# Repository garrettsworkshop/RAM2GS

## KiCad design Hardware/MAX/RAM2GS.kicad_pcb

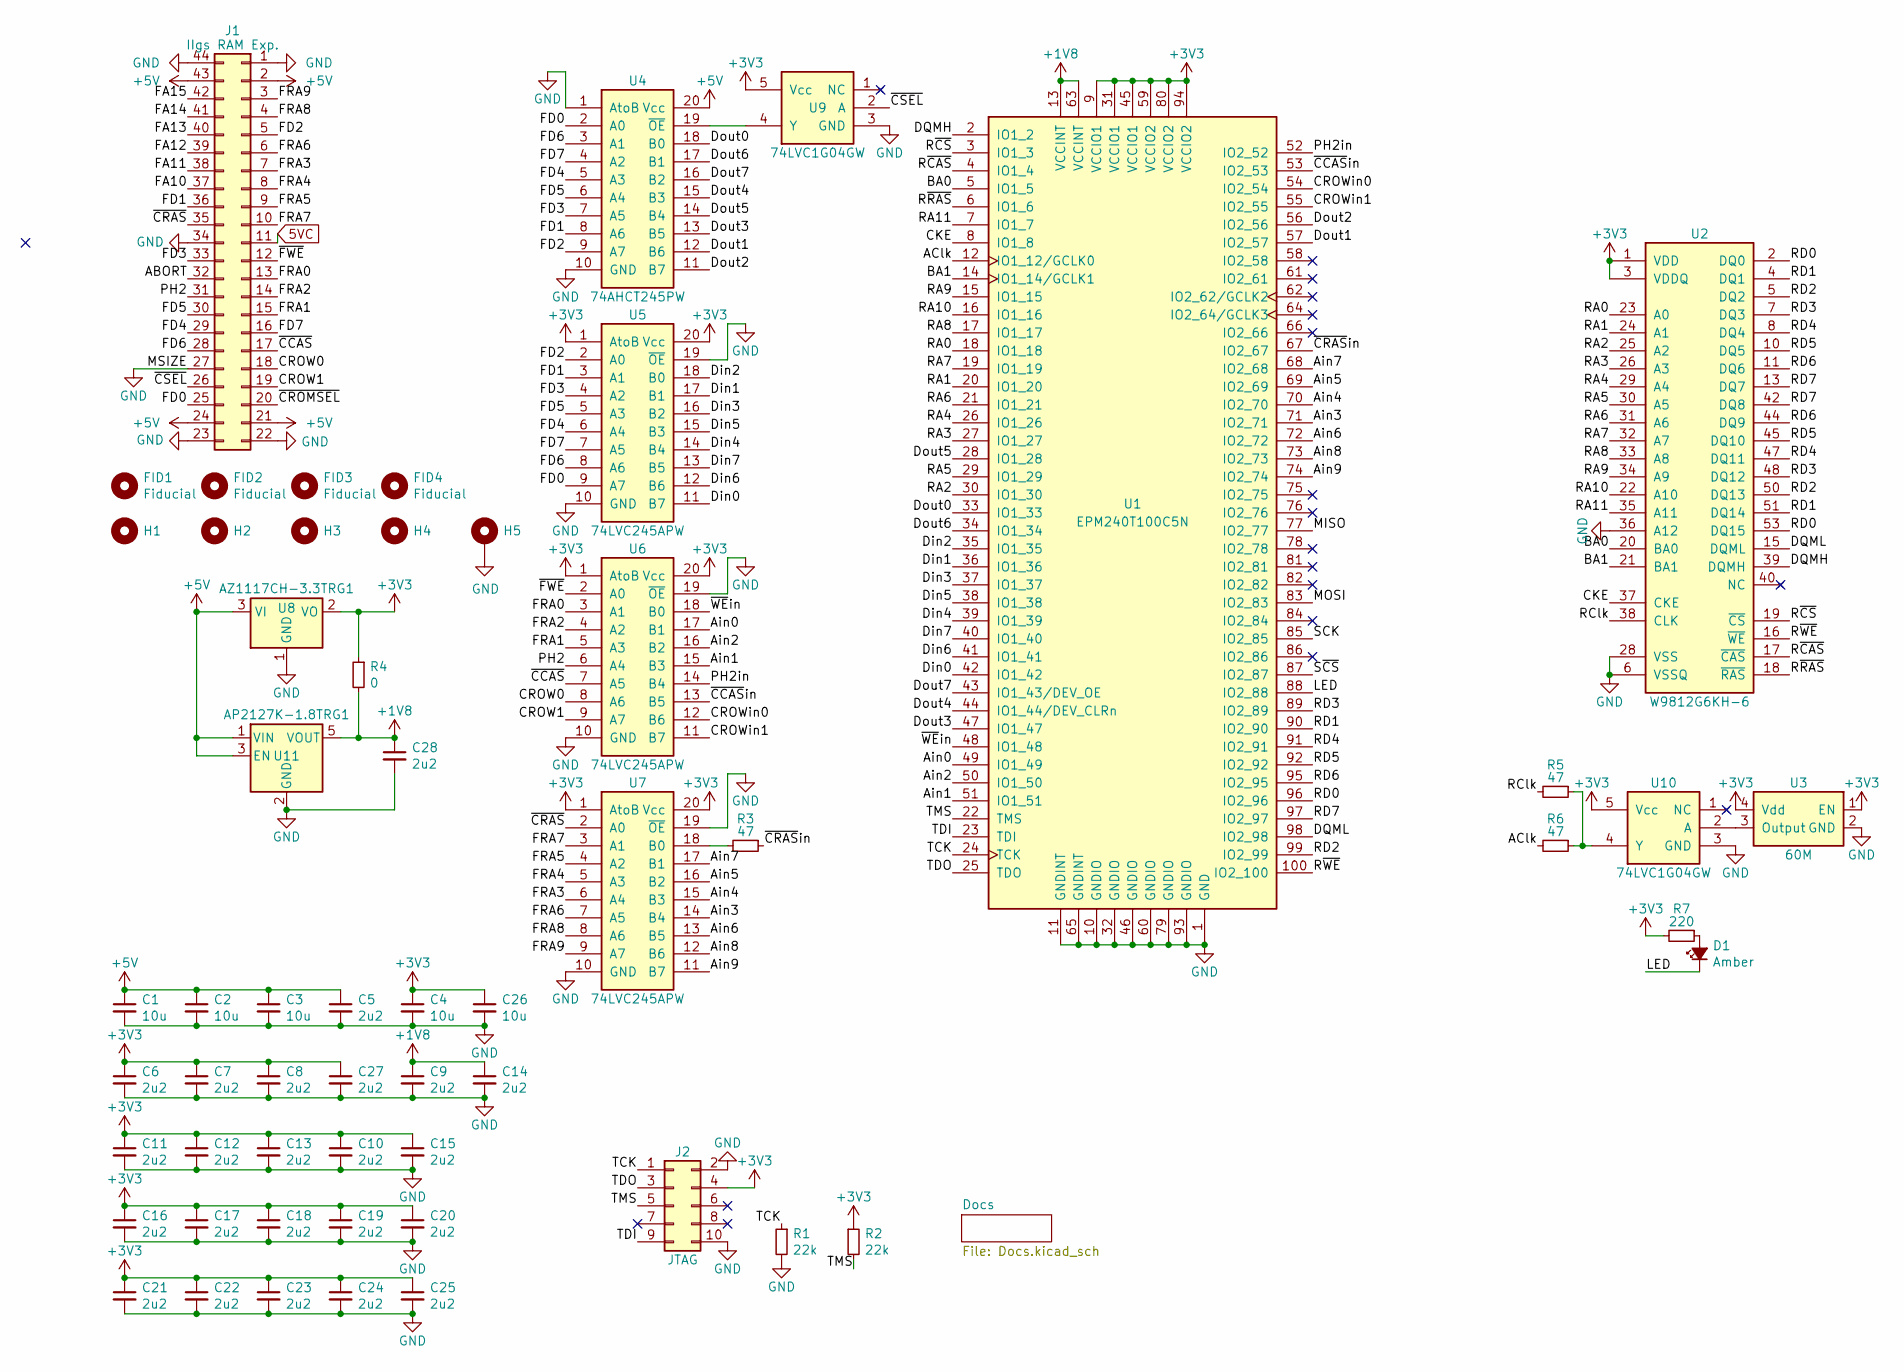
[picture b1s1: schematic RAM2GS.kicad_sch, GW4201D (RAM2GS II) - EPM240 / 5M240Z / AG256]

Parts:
C1, C2, C3, C4, C26: 10u; C_0805; LCSC Part C15850
C5, C6, C7, C8, C9, C10, C11, C12, C13, C14, C15, C16, C17, C18, C19, C20, C21, C22, C23, C24, C25, C27, C28: 2u2; C_0603; LCSC Part C23630
D1: Amber; LED_0805; LCSC Part C284932
FID1, FID2, FID3, FID4: Fiducial
H1, H2, H3, H4: PasteHole_1.152mm_NPTH
H5: PasteHole_1.1mm_PTH
J1: IIgs RAM Exp.; AppleIIgsMemoryExpansion_Edge
J2: JTAG; Tag-Connect_TC2050-IDC-FP_2x05_P1.27mm_Vertical
R1, R2: 22k; R_0805; LCSC Part C17560
R3, R5, R6: 47; R_0603; LCSC Part C23182
R4: 0; R_0805; LCSC Part C17477
R7: 220; R_0805; LCSC Part C17557
U1: EPM240T100C5N; TQFP-100_14x14mm_P0.5mm; LCSC Part C10041
U2: W9812G6KH-6; TSOP-II-54_22.2x10.16mm_P0.8mm; LCSC Part C62379
U3: 60M; Crystal_SMD_7050-4Pin_7.0x5.0mm_SiTime; LCSC Part C26255
U4: 74AHCT245PW; TSSOP-20_4.4x6.5mm_P0.65mm; LCSC Part C173388
U5, U6, U7: 74LVC245APW; TSSOP-20_4.4x6.5mm_P0.65mm; LCSC Part C6082
U8: AZ1117CH-3.3TRG1; SOT-223; LCSC Part C92102
U9, U10: 74LVC1G04GW; SOT-353; LCSC Part C10237
U11: AP2127K-1.8TRG1; SOT-23-5; LCSC Part C151375

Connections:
5VC: J1.11
+1V8: C9.1, C14.1, C28.1, R4.2, U1.13 (VCCINT), U1.63 (VCCINT), U11.5 (VOUT)
+3V3: C4.1, C6.1, C7.1, C8.1, C10.1, C11.1, C12.1, C13.1, C15.1, C16.1, C17.1, C18.1, C19.1, C20.1, C21.1, C22.1, C23.1, C24.1, C25.1, C26.1, C27.1, J2.4, R2.1, R4.1, R7.2, U1.9 (VCCIO1), U1.31 (VCCIO1), U1.45 (VCCIO1), U1.59 (VCCIO2), U1.80 (VCCIO2), U1.94 (VCCIO2), U2.1 (VDD), U2.3 (VDDQ), U2.9 (VDDQ), U2.14 (VDD), U2.27 (VDD), U2.43 (VDDQ), U2.49 (VDDQ), U3.1 (EN), U3.4 (Vdd), U5.1 (AtoB), U5.20 (Vcc), U6.1 (AtoB), U6.20 (Vcc), U7.1 (AtoB), U7.20 (Vcc), U8.2 (VO), U9.5 (Vcc), U10.5 (Vcc)
+5V: C1.1, C2.1, C3.1, C5.1, J1.2, J1.21, J1.24, J1.43, U4.20 (Vcc), U8.3 (VI), U11.1 (VIN), U11.3 (EN)
/ABORT: J1.32
/AClk: R6.2, U1.12 (IO1_12/GCLK0)
/Ain0: U1.49 (IO1_49), U6.17 (B1)
/Ain1: U1.51 (IO1_51), U6.15 (B3)
/Ain2: U1.50 (IO1_50), U6.16 (B2)
/Ain3: U1.71 (IO2_71), U7.14 (B4)
/Ain4: U1.70 (IO2_70), U7.15 (B3)
/Ain5: U1.69 (IO2_69), U7.16 (B2)
/Ain6: U1.72 (IO2_72), U7.13 (B5)
/Ain7: U1.68 (IO2_68), U7.17 (B1)
/Ain8: U1.73 (IO2_73), U7.12 (B6)
/Ain9: U1.74 (IO2_74), U7.11 (B7)
/BA0: U1.5 (IO1_5), U2.20 (BA0)
/BA1: U1.14 (IO1_14/GCLK1), U2.21 (BA1)
/CKE: U1.8 (IO1_8), U2.37 (CKE)
/CROW0: J1.18, U6.8 (A6)
/CROW1: J1.19, U6.9 (A7)
/CROWin0: U1.54 (IO2_54), U6.12 (B6)
/CROWin1: U1.55 (IO2_55), U6.11 (B7)
/DQMH: U1.2 (IO1_2), U2.39 (DQMH)
/DQML: U1.98 (IO2_98), U2.15 (DQML)
/Din0: U1.42 (IO1_42), U5.11 (B7)
/Din1: U1.36 (IO1_36), U5.17 (B1)
/Din2: U1.35 (IO1_35), U5.18 (B0)
/Din3: U1.37 (IO1_37), U5.16 (B2)
/Din4: U1.39 (IO1_39), U5.14 (B4)
/Din5: U1.38 (IO1_38), U5.15 (B3)
/Din6: U1.41 (IO1_41), U5.12 (B6)
/Din7: U1.40 (IO1_40), U5.13 (B5)
/Dout0: U1.33 (IO1_33), U4.18 (B0)
/Dout1: U1.57 (IO2_57), U4.12 (B6)
/Dout2: U1.56 (IO2_56), U4.11 (B7)
/Dout3: U1.47 (IO1_47), U4.13 (B5)
/Dout4: U1.44 (IO1_44/DEV_CLRn), U4.15 (B3)
/Dout5: U1.28 (IO1_28), U4.14 (B4)
/Dout6: U1.34 (IO1_34), U4.17 (B1)
/Dout7: U1.43 (IO1_43/DEV_OE), U4.16 (B2)
/FA10: J1.37
/FA11: J1.38
/FA12: J1.39
/FA13: J1.40
/FA14: J1.41
/FA15: J1.42
/FD0: J1.25, U4.2 (A0), U5.9 (A7)
/FD1: J1.36, U4.8 (A6), U5.3 (A1)
/FD2: J1.5, U4.9 (A7), U5.2 (A0)
/FD3: J1.33, U4.7 (A5), U5.4 (A2)
/FD4: J1.29, U4.5 (A3), U5.6 (A4)
/FD5: J1.30, U4.6 (A4), U5.5 (A3)
/FD6: J1.28, U4.3 (A1), U5.8 (A6)
/FD7: J1.16, U4.4 (A2), U5.7 (A5)
/FRA0: J1.13, U6.3 (A1)
/FRA1: J1.15, U6.5 (A3)
/FRA2: J1.14, U6.4 (A2)
/FRA3: J1.7, U7.6 (A4)
/FRA4: J1.8, U7.5 (A3)
/FRA5: J1.9, U7.4 (A2)
/FRA6: J1.6, U7.7 (A5)
/FRA7: J1.10, U7.3 (A1)
/FRA8: J1.4, U7.8 (A6)
/FRA9: J1.3, U7.9 (A7)
/LED: D1.1 (K), U1.88 (IO2_88)
/MISO: U1.77 (IO2_77)
/MOSI: U1.83 (IO2_83)
/PH2: J1.31, U6.6 (A4)
/PH2in: U1.52 (IO2_52), U6.14 (B4)
/RA0: U1.18 (IO1_18), U2.23 (A0)
/RA1: U1.20 (IO1_20), U2.24 (A1)
/RA2: U1.30 (IO1_30), U2.25 (A2)
/RA3: U1.27 (IO1_27), U2.26 (A3)
/RA4: U1.26 (IO1_26), U2.29 (A4)
/RA5: U1.29 (IO1_29), U2.30 (A5)
/RA6: U1.21 (IO1_21), U2.31 (A6)
/RA7: U1.19 (IO1_19), U2.32 (A7)
/RA8: U1.17 (IO1_17), U2.33 (A8)
/RA9: U1.15 (IO1_15), U2.34 (A9)
/RA10: U1.16 (IO1_16), U2.22 (A10)
/RA11: U1.7 (IO1_7), U2.35 (A11)
/RClk: R5.2, U2.38 (CLK)
/RD0: U1.96 (IO2_96), U2.2 (DQ0), U2.53 (DQ15)
/RD1: U1.90 (IO2_90), U2.4 (DQ1), U2.51 (DQ14)
/RD2: U1.99 (IO2_99), U2.5 (DQ2), U2.50 (DQ13)
/RD3: U1.89 (IO2_89), U2.7 (DQ3), U2.48 (DQ12)
/RD4: U1.91 (IO2_91), U2.8 (DQ4), U2.47 (DQ11)
/RD5: U1.92 (IO2_92), U2.10 (DQ5), U2.45 (DQ10)
/RD6: U1.95 (IO2_95), U2.11 (DQ6), U2.44 (DQ9)
/RD7: U1.97 (IO2_97), U2.13 (DQ7), U2.42 (DQ8)
/R~CAS: U1.4 (IO1_4), U2.17 (~CAS)
/R~CS: U1.3 (IO1_3), U2.19 (~CS)
/R~RAS: U1.6 (IO1_6), U2.18 (~RAS)
/R~WE: U1.100 (IO2_100), U2.16 (~WE)
/SCK: U1.85 (IO2_85)
/S~CS: U1.87 (IO2_87)
/TCK: J2.1, R1.1, U1.24 (TCK)
/TDI: J2.9, U1.23 (TDI)
/TDO: J2.3, U1.25 (TDO)
/TMS: J2.5, R2.2, U1.22 (TMS)
/~CCAS: J1.17, U6.7 (A5)
/~CCASin: U1.53 (IO2_53), U6.13 (B5)
/~CRAS: J1.35, U7.2 (A0)
/~CRASin: R3.1, U1.67 (IO2_67)
/~CROMSEL: J1.20
/~CSEL: J1.26, U9.2 (A)
/~FWE: J1.12, U6.2 (A0)
/~WEin: U1.48 (IO1_48), U6.18 (B0)
GND: C1.2, C2.2, C3.2, C4.2, C5.2, C6.2, C7.2, C8.2, C9.2, C10.2, C11.2, C12.2, C13.2, C14.2, C15.2, C16.2, C17.2, C18.2, C19.2, C20.2, C21.2, C22.2, C23.2, C24.2, C25.2, C26.2, C27.2, C28.2, H5.1, J1.1, J1.22, J1.23, J1.27, J1.34, J1.44, J2.2, J2.10, R1.2, U1.1 (GND), U1.10 (GNDIO), U1.11 (GNDINT), U1.32 (GNDIO), U1.46 (GNDIO), U1.60 (GNDIO), U1.65 (GNDINT), U1.79 (GNDIO), U1.93 (GNDIO), U2.6 (VSSQ), U2.12 (VSSQ), U2.28 (VSS), U2.36 (A12), U2.41 (VSS), U2.46 (VSSQ), U2.52 (VSSQ), U2.54 (VSS), U3.2 (GND), U4.1 (AtoB), U4.10 (GND), U5.10 (GND), U5.19 (~OE), U6.10 (GND), U6.19 (~OE), U7.10 (GND), U7.19 (~OE), U8.1 (GND), U9.3 (GND), U10.3 (GND), U11.2 (GND)
unnamed: D1.2 (A), R7.1
unnamed: U4.19 (~OE), U9.4 (Y)
unnamed: R3.2, U7.18 (B0)
unnamed: U3.3 (Output), U10.2 (A)
unnamed: R5.1, R6.1, U10.4 (Y)

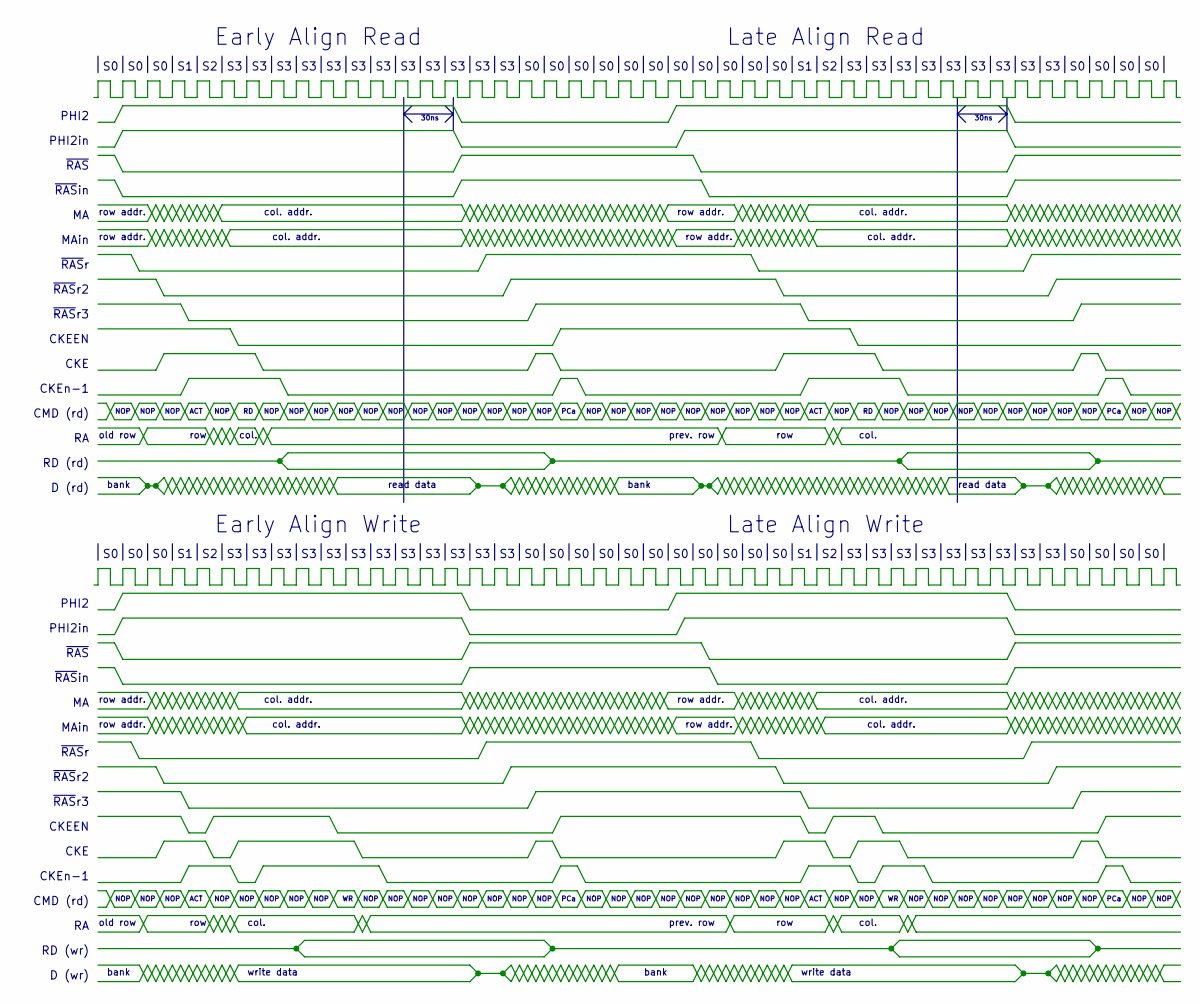
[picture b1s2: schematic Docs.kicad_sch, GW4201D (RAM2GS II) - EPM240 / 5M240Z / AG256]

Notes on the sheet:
NOP
~{RAS}r3
col.
30ns
~{RAS}r
~{RAS}in
Early Align Read
D (rd)
col. addr.
row addr.
prev. row
CKEn-1
PHI2
MAin
bank
~{RAS}r2
CMD (rd)
read data
Late Align Write
row
PHI2in
RD (wr)
PCa
write data
CKEEN
RD (rd)
Late Align Read
D (wr)
ACT
~{RAS}
CKE
old row
Early Align Write

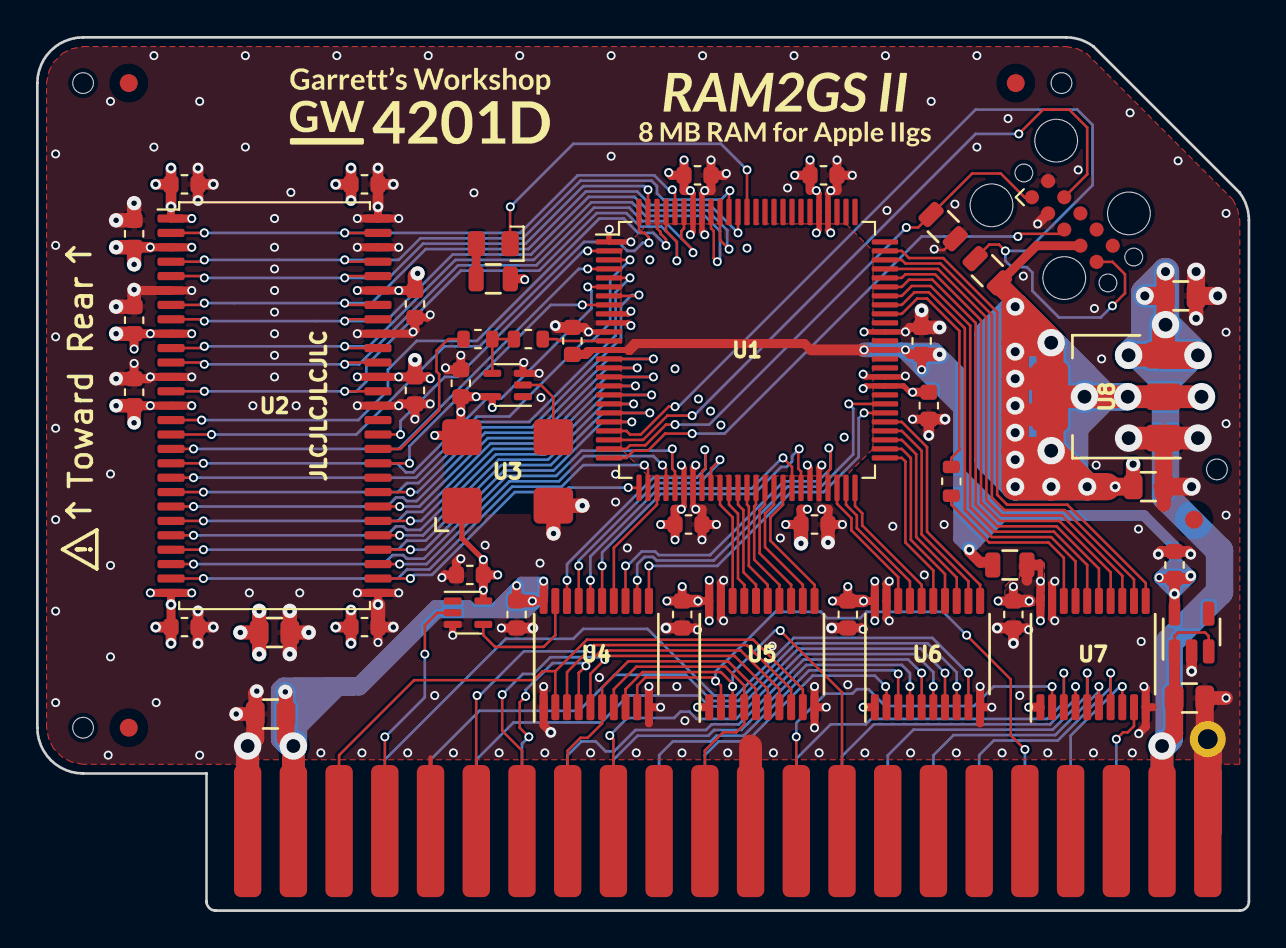
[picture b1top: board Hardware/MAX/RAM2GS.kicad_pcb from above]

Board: 4 copper layers, 67.3 x 48.5 mm, 58 parts (0 on the bottom side), 102 nets.

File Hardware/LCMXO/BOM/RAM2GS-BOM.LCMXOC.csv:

Reference, Quantity, Value, Footprint, Datasheet, Notes, LCSC Part, Mfg. Part Numbers
C30 ,1,15p,stdpads:C_0603,,"10V or higher. Any manufacturer's part is acceptable but Samsung, Murata, Yageo preferred.",C1644,Samsung CL10C150JB8NNNC
C1 C2 C3 C4 C26 ,5,10u,stdpads:C_0805,,"10V or higher. Any manufacturer's part is acceptable but Samsung, Murata, Yageo preferred.",C15850,Samsung CL21A106KAYNNNE
C5 C6 C7 C8 C9 C10 C11 C12 C13 C14 C15 C16 C17 C18 C19 C20 C21 C22 C23 C24 C25 C27 C28 C29 ,24,2u2,stdpads:C_0603,,"10V or higher. Any manufacturer's part is acceptable but Samsung, Murata, Yageo preferred.",C23630,Samsung CL10A225KO8NNNC
D1 ,1,Amber,stdpads:LED_0805,,Any manufacturer's part is acceptable.,,
FID1 FID2 FID3 FID4 ,4,Fiducial,stdpads:Fiducial,,DNP - SMT vision system fiducial,,
H1 H2 H4 H5 ,4, ,stdpads:PasteHole_1.152mm_NPTH,,DNP - mounting hole for solder paste printing,,
H3 ,1, ,stdpads:PasteHole_1.1mm_PTH,,DNP - mounting hole,,
J1 ,1,IIgs RAM Exp.,stdpads:AppleIIgsMemoryExpansion_Edge,,DNP - edge connector,,
J2 ,1,JTAG,Connector:Tag-Connect_TC2050-IDC-FP_2x05_P1.27mm_Vertical,,DNP - test pad connector,,
R1 R2 ,2,22k,stdpads:R_0805,,Any manufacturer's part is acceptable.,C17560,Uniroyal 0805W8F2202T5E
R4 ,1,0,stdpads:R_0805,,Any manufacturer's part is acceptable.,C17477,Uniroyal 0805W8F0000T5E
R3 R5 R6 R7 ,4,47,stdpads:R_0603,,Any manufacturer's part is acceptable.,C23182,Uniroyal 0603WAF470JT5E
R8 ,1,220,stdpads:R_0805,,Any manufacturer's part is acceptable.,C17557,Uniroyal 0805W8F2200T5E
U1 ,1,LCMXO256C-TN100,stdpads:TQFP-100_14x14mm_P0.5mm,,,C1550734,"Lattice LCMXO256C-3TN100C, Lattice LCMXO256C-4TN100C, Lattice LCMXO256C-5TN100C, Lattice LCMXO256C-3TN100I, Lattice LCMXO256C-4TN100I, Lattice LCMXO640C-3TN100C, Lattice LCMXO640C-4TN100C, Lattice LCMXO640C-5TN100C, Lattice LCMXO640C-3TN100I, Lattice LCMXO640C-4TN100I"
U9 U10 ,2,74LVC1G04GW,stdpads:SOT-353,,Most 74LVC1G04 or 74AHC1G04 in SOT-353 package is acceptable.,C10237,"NXP 74LVC1G04GW, TI SN74LVC1G04DCK, NXP 74AHC1G04GW, TI SN74AHC1G04DCK"
U11 ,1,DNP,stdpads:SOT-23-5,,,,
U12 ,1,25F010,stdpads:SOIC-8_3.9mm,,Most SPI flash in SOIC-8 (3.9mm / 150 mil width) package is acceptable.,C2687406,"Zetta ZD25WD20BTIGT, Adesto AT25SF081-SSHD, Winbond W25X20CLSNIG"
U2 ,1,W9812G6KH-6,stdpads:TSOP-II-54_22.2x10.16mm_P0.8mm,,Most 166 MHz 128/256 Mbit x16 SDRAM is acceptable.,C62379,"Winbond W9812G6KH-6, Winbond W9812G6KH-6I, Winbond W9825G6KH-6, Winbond W9825G6KH-6I, ISSI IS42S16160J-6TL, ISSI IS42S16160J-6TLI, Micron MT48LC16M16A2P-6A :G, Micron MT48LC16M16A2P-6A IT:G"
U3 ,1,60M,stdpads:Crystal_SMD_7050-4Pin_7.0x5.0mm_SiTime,,Most 60-62.5 MHz 3.3V crystal oscillator or silicon oscillator is acceptable. Do not use crystal resonator or ceramic resonator.,C26255,"SiTime SIT1602AI-82-33E-60.000000Y, Shenzhen SCTF S7D60.000000B20F30T, Taiten OCETGLJTNF-60MHZ"
U4 ,1,74AHCT245PW,stdpads:TSSOP-20_4.4x6.5mm_P0.65mm,,Most 74AHCT245 in TSSOP-20 package is acceptable.,C173388,"NXP 74AHCT245PW, NXP 74AHCT245APW, TI SN74AHCT245PW"
U5 U6 U7 ,3,74LVC245APW,stdpads:TSSOP-20_4.4x6.5mm_P0.65mm,,Most 74LVC245 or 74AHC245 in TSSOP-20 package is acceptable.,C6082,"NXP 74LVC245APW, TI SN74LVC245APW, NXP 74AHC245PW, NXP 74AHC245APW, TI SN74AHC245PW"
U8 ,1,AZ1117CH-3.3TRG1,stdpads:SOT-223,,Most 1117-type 3.3V regulator in SOT-223 package is acceptable.,C92102,"Diodes AZ1117CH-3.3TRG1, Diodes AZ1117EH-3.3TRG1"

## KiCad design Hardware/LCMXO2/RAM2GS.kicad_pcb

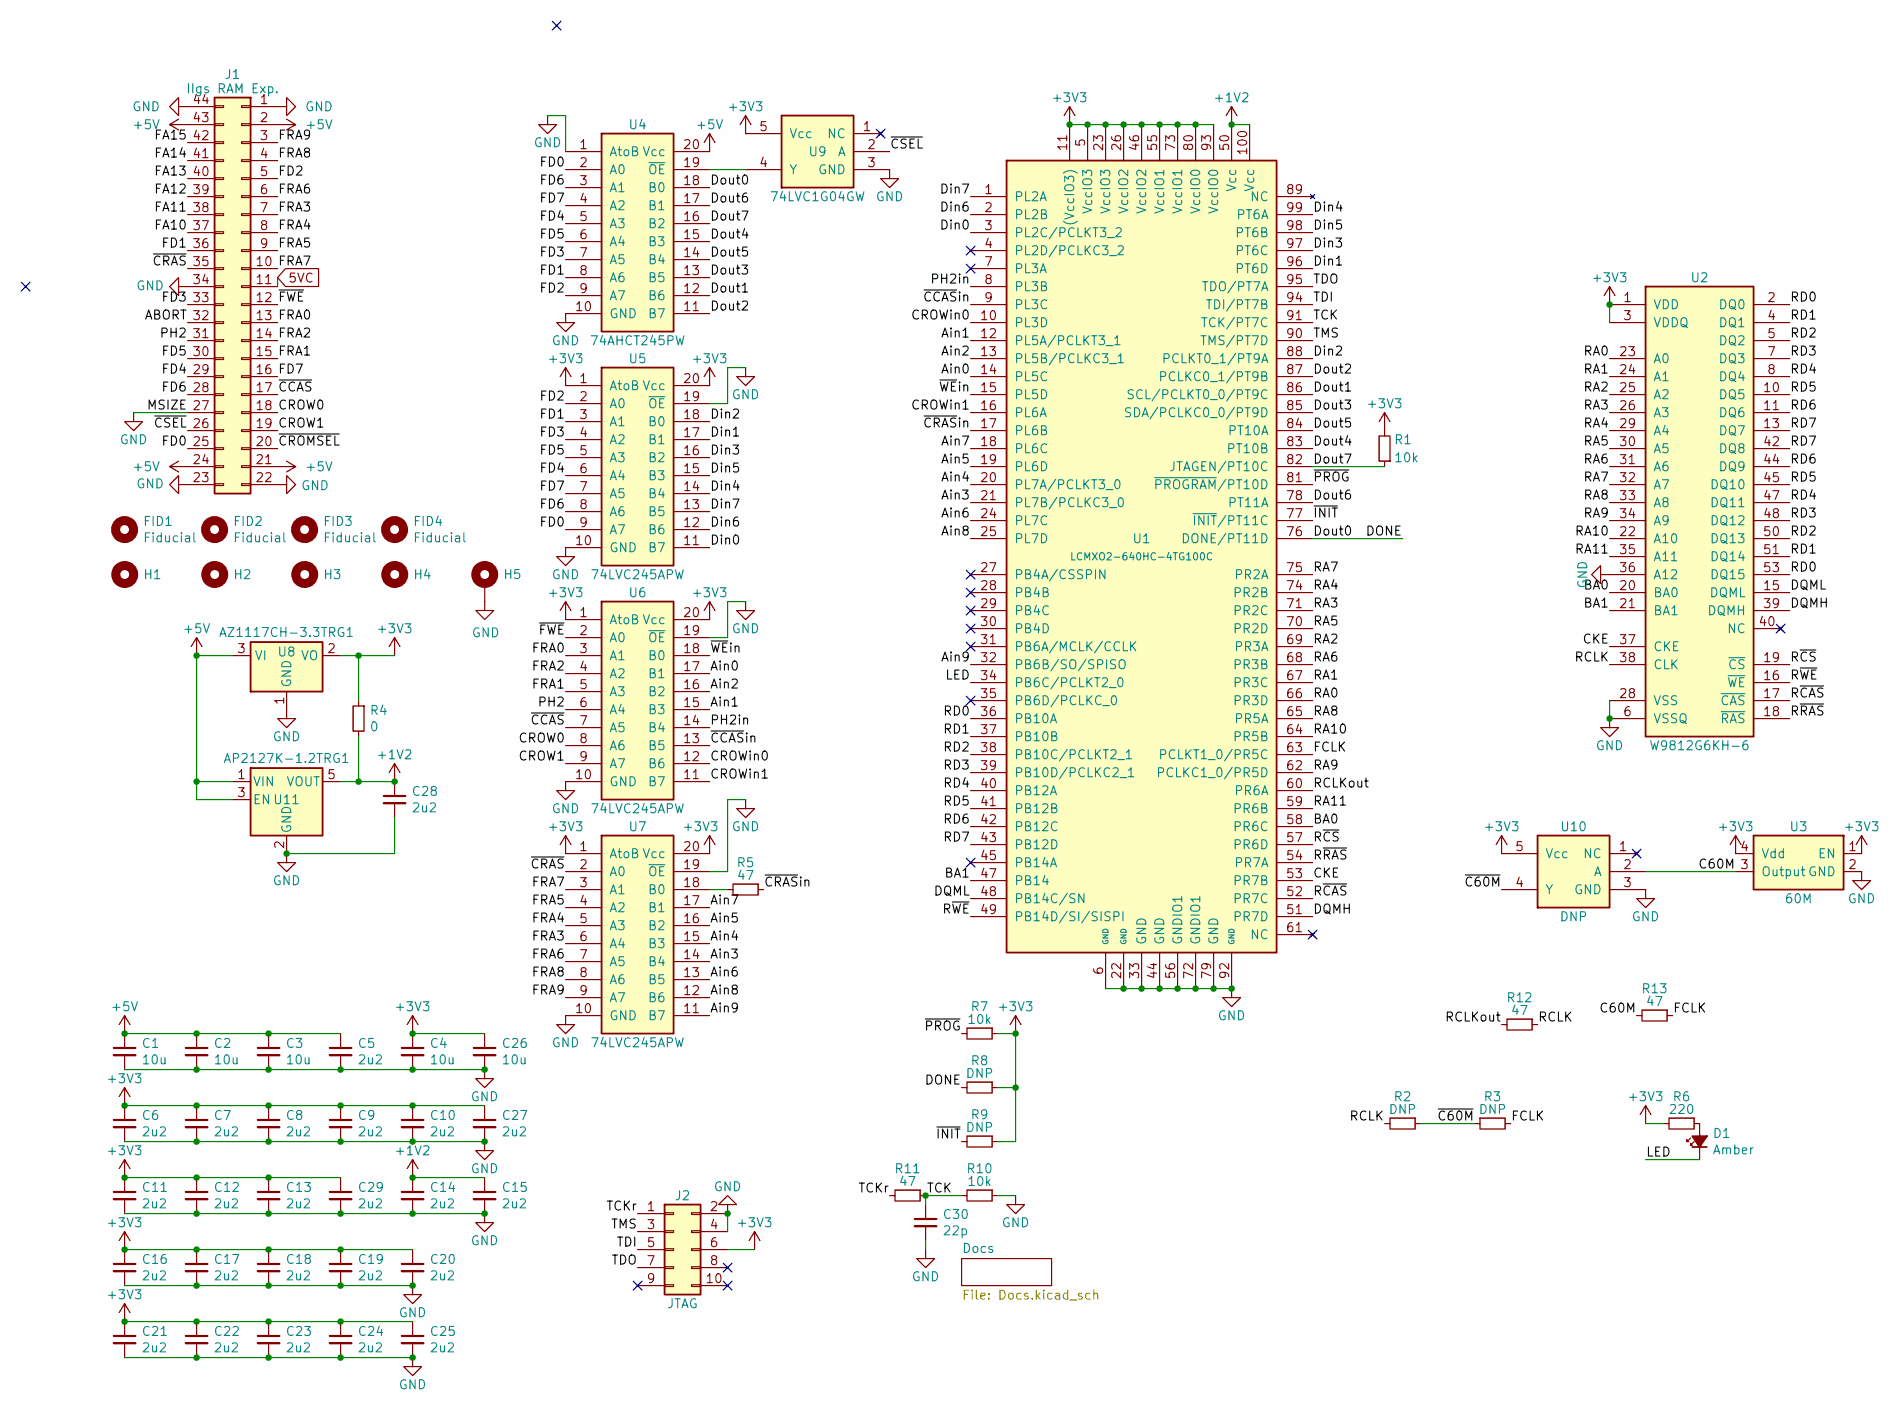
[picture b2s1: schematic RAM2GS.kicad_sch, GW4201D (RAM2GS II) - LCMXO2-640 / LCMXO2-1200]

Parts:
C1, C2, C3, C4, C26: 10u; C_0805; LCSC Part C15850
C5, C6, C7, C8, C9, C10, C11, C12, C13, C14, C15, C16, C17, C18, C19, C20, C21, C22, C23, C24, C25, C27, C28, C29: 2u2; C_0603; LCSC Part C23630
C30: 22p; C_0603; LCSC Part C1653
D1: Amber; LED_0805; LCSC Part C284932
FID1, FID2, FID3, FID4: Fiducial
H1, H2, H3, H4: PasteHole_1.152mm_NPTH
H5: PasteHole_1.1mm_PTH
J1: IIgs RAM Exp.; AppleIIgsMemoryExpansion_Edge
J2: JTAG; Tag-Connect_TC2050-IDC-FP_2x05_P1.27mm_Vertical
R1, R7, R10: 10k; R_0603; LCSC Part C25804
R2, R3, R8, R9: DNP; R_0603
R4: 0; R_0805; LCSC Part C17477
R5, R11, R12, R13: 47; R_0603; LCSC Part C23182
R6: 220; R_0805; LCSC Part C17557
U1: LCMXO2-640HC-4TG100C; TQFP-100_14x14mm_P0.5mm; LCSC Part C1519051
U2: W9812G6KH-6; TSOP-II-54_22.2x10.16mm_P0.8mm; LCSC Part C62379
U3: 60M; Crystal_SMD_7050-4Pin_7.0x5.0mm_SiTime; LCSC Part C26255
U4: 74AHCT245PW; TSSOP-20_4.4x6.5mm_P0.65mm; LCSC Part C173388
U5, U6, U7: 74LVC245APW; TSSOP-20_4.4x6.5mm_P0.65mm; LCSC Part C6082
U8: AZ1117CH-3.3TRG1; SOT-223; LCSC Part C92102
U9: 74LVC1G04GW; SOT-353; LCSC Part C10237
U10: DNP; SOT-353
U11: AP2127K-1.2TRG1; SOT-23-5; LCSC Part C151376

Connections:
5VC: J1.11
+1V2: C14.1, C15.1, C28.1, R4.2, U1.50 (Vcc), U1.100 (Vcc), U11.5 (VOUT)
+3V3: C4.1, C6.1, C7.1, C8.1, C9.1, C10.1, C11.1, C12.1, C13.1, C16.1, C17.1, C18.1, C19.1, C20.1, C21.1, C22.1, C23.1, C24.1, C25.1, C26.1, C27.1, C29.1, J2.6, R1.2, R4.1, R6.2, R7.1, R8.1, R9.1, U1.5 (VccIO3), U1.11 ((VccIO3)), U1.23 (VccIO3), U1.26 (VccIO2), U1.46 (VccIO2), U1.55 (VccIO1), U1.73 (VccIO1), U1.80 (VccIO0), U1.93 (VccIO0), U2.1 (VDD), U2.3 (VDDQ), U2.9 (VDDQ), U2.14 (VDD), U2.27 (VDD), U2.43 (VDDQ), U2.49 (VDDQ), U3.1 (EN), U3.4 (Vdd), U5.1 (AtoB), U5.20 (Vcc), U6.1 (AtoB), U6.20 (Vcc), U7.1 (AtoB), U7.20 (Vcc), U8.2 (VO), U9.5 (Vcc), U10.5 (Vcc)
+5V: C1.1, C2.1, C3.1, C5.1, J1.2, J1.21, J1.24, J1.43, U4.20 (Vcc), U8.3 (VI), U11.1 (VIN), U11.3 (EN)
/ABORT: J1.32
/Ain0: U1.14 (PL5C), U6.17 (B1)
/Ain1: U1.12 (PL5A/PCLKT3_1), U6.15 (B3)
/Ain2: U1.13 (PL5B/PCLKC3_1), U6.16 (B2)
/Ain3: U1.21 (PL7B/PCLKC3_0), U7.14 (B4)
/Ain4: U1.20 (PL7A/PCLKT3_0), U7.15 (B3)
/Ain5: U1.19 (PL6D), U7.16 (B2)
/Ain6: U1.24 (PL7C), U7.13 (B5)
/Ain7: U1.18 (PL6C), U7.17 (B1)
/Ain8: U1.25 (PL7D), U7.12 (B6)
/Ain9: U1.32 (PB6B/SO/SPISO), U7.11 (B7)
/BA0: U1.58 (PR6C), U2.20 (BA0)
/BA1: U1.47 (PB14), U2.21 (BA1)
/C60M: R13.2, U3.3 (Output), U10.2 (A)
/CKE: U1.53 (PR7B), U2.37 (CKE)
/CROW0: J1.18, U6.8 (A6)
/CROW1: J1.19, U6.9 (A7)
/CROWin0: U1.10 (PL3D), U6.12 (B6)
/CROWin1: U1.16 (PL6A), U6.11 (B7)
/DONE: R8.2, U1.76 (DONE/PT11D), U4.18 (B0)
/DQMH: U1.51 (PR7D), U2.39 (DQMH)
/DQML: U1.48 (PB14C/SN), U2.15 (DQML)
/Din0: U1.3 (PL2C/PCLKT3_2), U5.11 (B7)
/Din1: U1.96 (PT6D), U5.17 (B1)
/Din2: U1.88 (PCLKT0_1/PT9A), U5.18 (B0)
/Din3: U1.97 (PT6C), U5.16 (B2)
/Din4: U1.99 (PT6A), U5.14 (B4)
/Din5: U1.98 (PT6B), U5.15 (B3)
/Din6: U1.2 (PL2B), U5.12 (B6)
/Din7: U1.1 (PL2A), U5.13 (B5)
/Dout1: U1.86 (SCL/PCLKT0_0/PT9C), U4.12 (B6)
/Dout2: U1.87 (PCLKC0_1/PT9B), U4.11 (B7)
/Dout3: U1.85 (SDA/PCLKC0_0/PT9D), U4.13 (B5)
/Dout4: U1.83 (PT10B), U4.15 (B3)
/Dout5: U1.84 (PT10A), U4.14 (B4)
/Dout6: U1.78 (PT11A), U4.17 (B1)
/Dout7: R1.1, U1.82 (JTAGEN/PT10C), U4.16 (B2)
/FA10: J1.37
/FA11: J1.38
/FA12: J1.39
/FA13: J1.40
/FA14: J1.41
/FA15: J1.42
/FCLK: R3.2, R13.1, U1.63 (PCLKT1_0/PR5C)
/FD0: J1.25, U4.2 (A0), U5.9 (A7)
/FD1: J1.36, U4.8 (A6), U5.3 (A1)
/FD2: J1.5, U4.9 (A7), U5.2 (A0)
/FD3: J1.33, U4.7 (A5), U5.4 (A2)
/FD4: J1.29, U4.5 (A3), U5.6 (A4)
/FD5: J1.30, U4.6 (A4), U5.5 (A3)
/FD6: J1.28, U4.3 (A1), U5.8 (A6)
/FD7: J1.16, U4.4 (A2), U5.7 (A5)
/FRA0: J1.13, U6.3 (A1)
/FRA1: J1.15, U6.5 (A3)
/FRA2: J1.14, U6.4 (A2)
/FRA3: J1.7, U7.6 (A4)
/FRA4: J1.8, U7.5 (A3)
/FRA5: J1.9, U7.4 (A2)
/FRA6: J1.6, U7.7 (A5)
/FRA7: J1.10, U7.3 (A1)
/FRA8: J1.4, U7.8 (A6)
/FRA9: J1.3, U7.9 (A7)
/LED: D1.1 (K), U1.34 (PB6C/PCLKT2_0)
/PH2: J1.31, U6.6 (A4)
/PH2in: U1.8 (PL3B), U6.14 (B4)
/RA0: U1.66 (PR3D), U2.23 (A0)
/RA1: U1.67 (PR3C), U2.24 (A1)
/RA2: U1.69 (PR3A), U2.25 (A2)
/RA3: U1.71 (PR2C), U2.26 (A3)
/RA4: U1.74 (PR2B), U2.29 (A4)
/RA5: U1.70 (PR2D), U2.30 (A5)
/RA6: U1.68 (PR3B), U2.31 (A6)
/RA7: U1.75 (PR2A), U2.32 (A7)
/RA8: U1.65 (PR5A), U2.33 (A8)
/RA9: U1.62 (PCLKC1_0/PR5D), U2.34 (A9)
/RA10: U1.64 (PR5B), U2.22 (A10)
/RA11: U1.59 (PR6B), U2.35 (A11)
/RCLK: R2.2, R12.1, U2.38 (CLK)
/RCLKout: R12.2, U1.60 (PR6A)
/RD0: U1.36 (PB10A), U2.2 (DQ0), U2.53 (DQ15)
/RD1: U1.37 (PB10B), U2.4 (DQ1), U2.51 (DQ14)
/RD2: U1.38 (PB10C/PCLKT2_1), U2.5 (DQ2), U2.50 (DQ13)
/RD3: U1.39 (PB10D/PCLKC2_1), U2.7 (DQ3), U2.48 (DQ12)
/RD4: U1.40 (PB12A), U2.8 (DQ4), U2.47 (DQ11)
/RD5: U1.41 (PB12B), U2.10 (DQ5), U2.45 (DQ10)
/RD6: U1.42 (PB12C), U2.11 (DQ6), U2.44 (DQ9)
/RD7: U1.43 (PB12D), U2.13 (DQ7), U2.42 (DQ8)
/R~CAS: U1.52 (PR7C), U2.17 (~CAS)
/R~CS: U1.57 (PR6D), U2.19 (~CS)
/R~RAS: U1.54 (PR7A), U2.18 (~RAS)
/R~WE: U1.49 (PB14D/SI/SISPI), U2.16 (~WE)
/TCK: C30.1, R10.2, R11.1, U1.91 (TCK/PT7C)
/TCKr: J2.1, R11.2
/TDI: J2.5, U1.94 (TDI/PT7B)
/TDO: J2.7, U1.95 (TDO/PT7A)
/TMS: J2.3, U1.90 (TMS/PT7D)
/~C60M: R2.1, R3.1, U10.4 (Y)
/~CCAS: J1.17, U6.7 (A5)
/~CCASin: U1.9 (PL3C), U6.13 (B5)
/~CRAS: J1.35, U7.2 (A0)
/~CRASin: R5.1, U1.17 (PL6B)
/~CROMSEL: J1.20
/~CSEL: J1.26, U9.2 (A)
/~FWE: J1.12, U6.2 (A0)
/~INIT: R9.2, U1.77 (~INIT/PT11C)
/~PROG: R7.2, U1.81 (~PROGRAM/PT10D)
/~WEin: U1.15 (PL5D), U6.18 (B0)
GND: C1.2, C2.2, C3.2, C4.2, C5.2, C6.2, C7.2, C8.2, C9.2, C10.2, C11.2, C12.2, C13.2, C14.2, C15.2, C16.2, C17.2, C18.2, C19.2, C20.2, C21.2, C22.2, C23.2, C24.2, C25.2, C26.2, C27.2, C28.2, C29.2, C30.2, H5.1, J1.1, J1.22, J1.23, J1.27, J1.34, J1.44, J2.2, J2.4, R10.1, U1.6 (GND), U1.22 (GND), U1.33 (GND), U1.44 (GND), U1.56 (GNDIO1), U1.72 (GNDIO1), U1.79 (GND), U1.92 (GND), U2.6 (VSSQ), U2.12 (VSSQ), U2.28 (VSS), U2.36 (A12), U2.41 (VSS), U2.46 (VSSQ), U2.52 (VSSQ), U2.54 (VSS), U3.2 (GND), U4.1 (AtoB), U4.10 (GND), U5.10 (GND), U5.19 (~OE), U6.10 (GND), U6.19 (~OE), U7.10 (GND), U7.19 (~OE), U8.1 (GND), U9.3 (GND), U10.3 (GND), U11.2 (GND)
unnamed: D1.2 (A), R6.1
unnamed: U4.19 (~OE), U9.4 (Y)
unnamed: R5.2, U7.18 (B0)

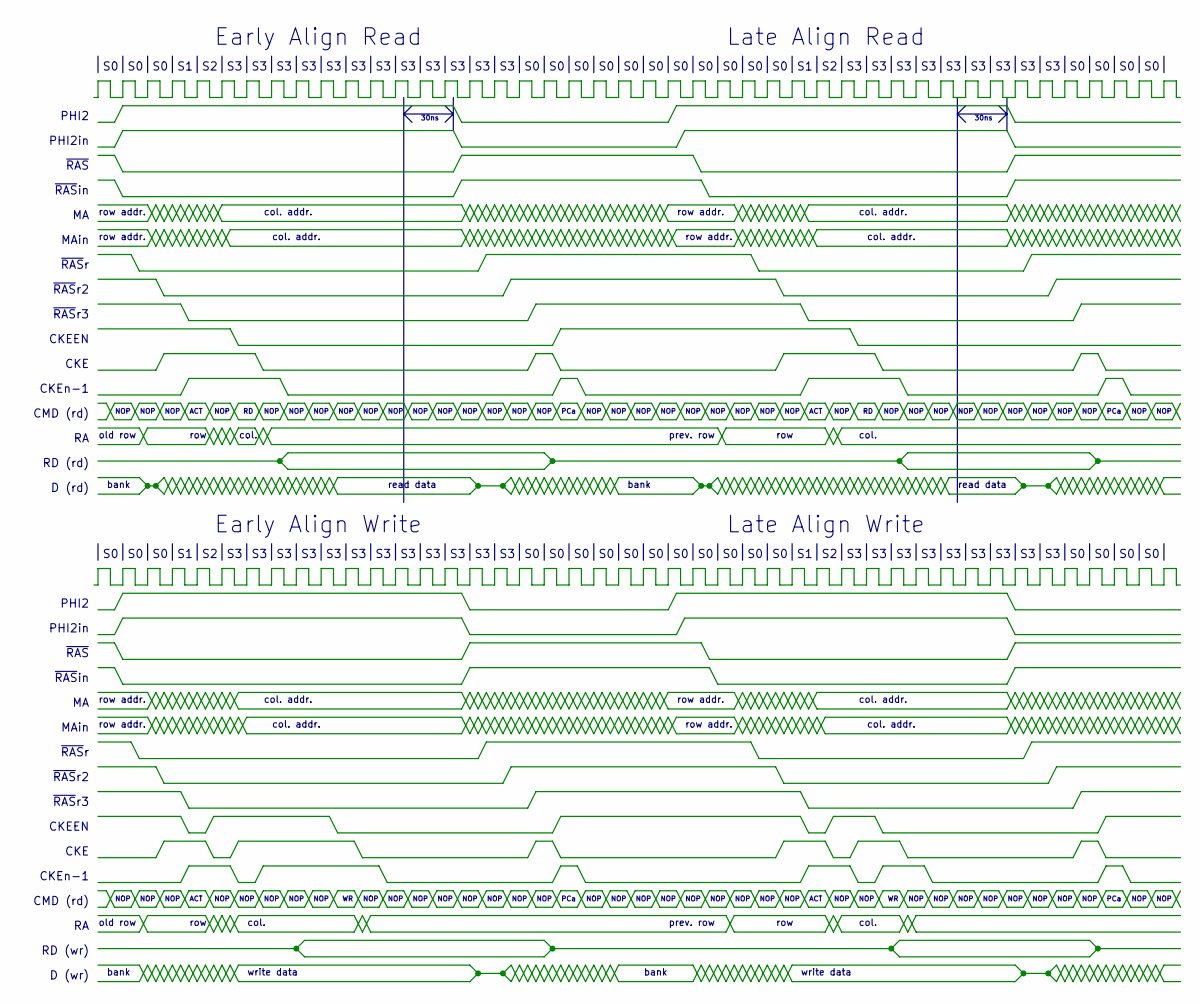
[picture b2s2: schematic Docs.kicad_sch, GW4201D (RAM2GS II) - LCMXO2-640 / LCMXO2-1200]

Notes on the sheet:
col. addr.
CKE
30ns
NOP
~{RAS}r3
row
row addr.
~{RAS}
PHI2
CMD (rd)
~{RAS}r2
PCa
ACT
read data
PHI2in
D (wr)
CKEn-1
col.
D (rd)
RD (wr)
Early Align Write
Late Align Write
~{RAS}r
bank
write data
CKEEN
Early Align Read
~{RAS}in
MAin
Late Align Read
old row
prev. row
RD (rd)

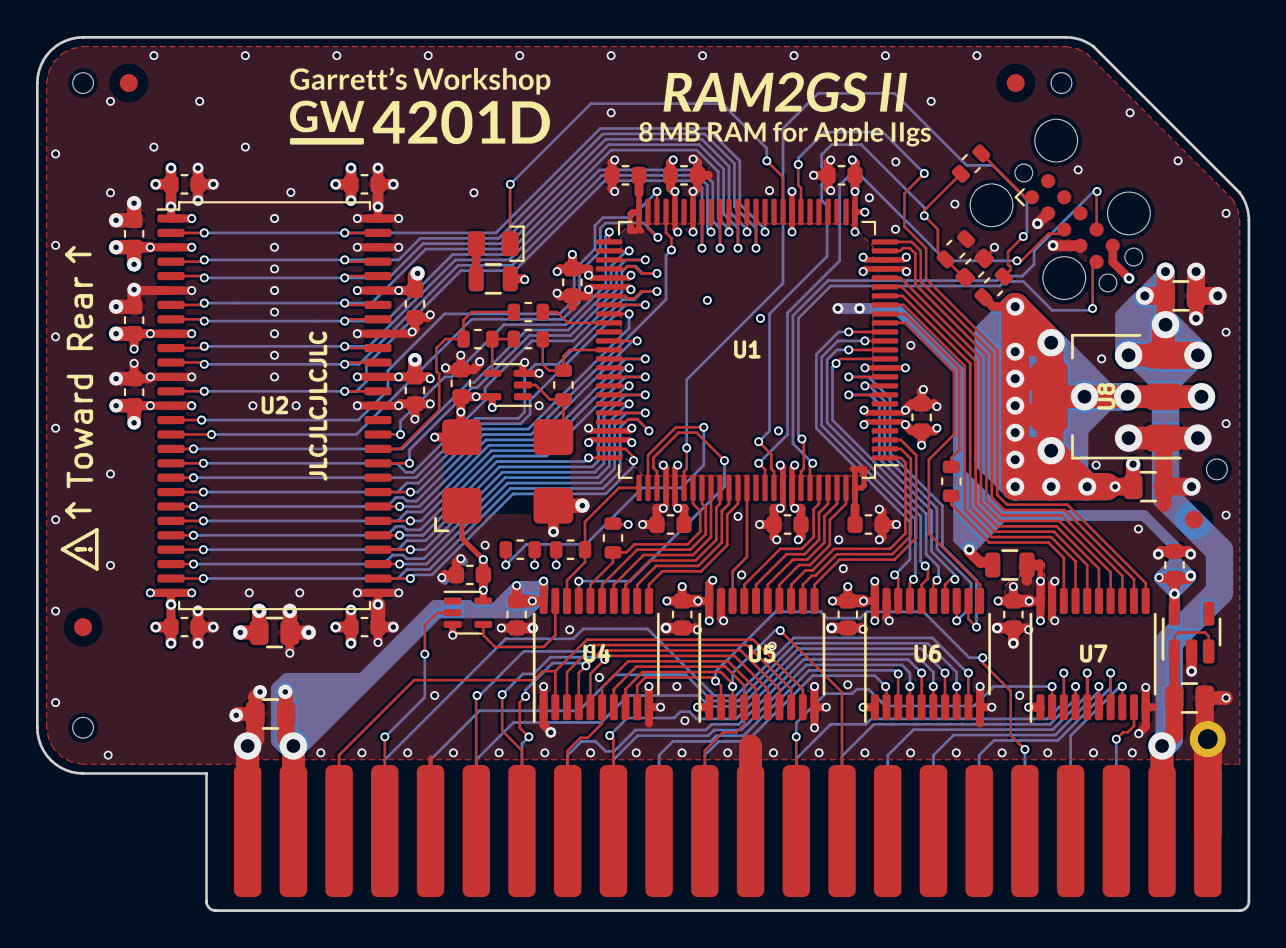
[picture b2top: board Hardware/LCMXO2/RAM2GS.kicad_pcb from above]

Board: 4 copper layers, 67.3 x 48.5 mm, 66 parts (0 on the bottom side), 106 nets.

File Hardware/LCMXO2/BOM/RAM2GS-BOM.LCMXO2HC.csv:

Reference, Quantity, Value, Footprint, Datasheet, Notes, LCSC Part, Mfg. Part Numbers
C30 ,1,15p,stdpads:C_0603,,"10V or higher. Any manufacturer's part is acceptable but Samsung, Murata, Yageo preferred.",C1644,Samsung CL10C150JB8NNNC
C1 C2 C3 C4 C26 ,5,10u,stdpads:C_0805,,"10V or higher. Any manufacturer's part is acceptable but Samsung, Murata, Yageo preferred.",C15850,Samsung CL21A106KAYNNNE
C5 C6 C7 C8 C9 C10 C11 C12 C13 C14 C15 C16 C17 C18 C19 C20 C21 C22 C23 C24 C25 C27 C28 C29 ,24,2u2,stdpads:C_0603,,"10V or higher. Any manufacturer's part is acceptable but Samsung, Murata, Yageo preferred.",C23630,Samsung CL10A225KO8NNNC
D1 ,1,Amber,stdpads:LED_0805,,Any manufacturer's part is acceptable.,,
FID1 FID2 FID3 FID4 ,4,Fiducial,stdpads:Fiducial,,DNP - SMT vision system fiducial,,
H1 H2 H4 H5 ,4, ,stdpads:PasteHole_1.152mm_NPTH,,DNP - mounting hole for solder paste printing,,
H3 ,1, ,stdpads:PasteHole_1.1mm_PTH,,DNP - mounting hole,,
J1 ,1,Memory Expansion,stdpads:AppleIIgsMemoryExpansion_Edge,,DNP - edge connector,,
J2 ,1,JTAG,Connector:Tag-Connect_TC2050-IDC-FP_2x05_P1.27mm_Vertical,,DNP - test pad connector,,
R1 R7 R8 R9 R10 ,5,10k,stdpads:R_0603,,Any manufacturer's part is acceptable.,C25804,Uniroyal 0603WAF1002T5E
R2 R3 R5 R11 R12 R13 ,4,47,stdpads:R_0603,,Any manufacturer's part is acceptable.,C23182,Uniroyal 0603WAF470JT5E
R4 ,1,0,stdpads:R_0805,,Any manufacturer's part is acceptable.,C17477,Uniroyal 0805W8F0000T5E
R6 ,1,220,stdpads:R_0805,,Any manufacturer's part is acceptable.,C17557,Uniroyal 0805W8F2200T5E
U1 ,1,LCMXO2HC-TG100,stdpads:TQFP-100_14x14mm_P0.5mm,,,C1519051,"Lattice LCMXO2-640HC-4TG100C, Lattice LCMXO2-640HC-5TG100C, Lattice LCMXO2-640HC-6TG100C, Lattice LCMXO2-640HC-4TG100I, Lattice LCMXO2-640HC-5TG100I, Lattice LCMXO2-640HC-6TG100I, Lattice LCMXO2-1200HC-4TG100C, Lattice LCMXO2-1200HC-5TG100C, Lattice LCMXO2-1200HC-6TG100C, Lattice LCMXO2-1200HC-4TG100I, Lattice LCMXO2-1200HC-5TG100I, Lattice LCMXO2-1200HC-6TG100I"
U9 U10 ,2,74LVC1G04GW,stdpads:SOT-353,,Most 74LVC1G04 or 74AHC1G04 in SOT-353 package is acceptable.,C10237,"NXP 74LVC1G04GW, TI SN74LVC1G04DCK"
U11 ,1,DNP,stdpads:SOT-23-5,,,,
U2 ,1,W9812G6KH-6,stdpads:TSOP-II-54_22.2x10.16mm_P0.8mm,,Most 166 MHz 128/256 Mbit x16 SDRAM is acceptable.,C62379,"Winbond W9812G6KH-6, Winbond W9812G6KH-6I, Winbond W9825G6KH-6, Winbond W9825G6KH-6I, ISSI IS42S16160J-6TL, ISSI IS42S16160J-6TLI, Micron MT48LC16M16A2P-6A :G, Micron MT48LC16M16A2P-6A IT:G"
U3 ,1,60M,stdpads:Crystal_SMD_7050-4Pin_7.0x5.0mm_SiTime,,Most 60-62.5 MHz 3.3V crystal oscillator or silicon oscillator is acceptable. Do not use crystal resonator or ceramic resonator.,C26255,"SiTime SIT1602AI-82-33E-60.000000Y, Shenzhen SCTF S7D60.000000B20F30T, Taiten OCETGLJTNF-60MHZ"
U4 ,1,74AHCT245PW,stdpads:TSSOP-20_4.4x6.5mm_P0.65mm,,Most 74AHCT245 in TSSOP-20 package is acceptable.,C173388,"NXP 74AHCT245PW, TI SN74AHCT245PW"
U5 U6 U7 ,3,74LVC245APW,stdpads:TSSOP-20_4.4x6.5mm_P0.65mm,,Most 74LVC245 or 74AHC245 in TSSOP-20 package is acceptable.,C6082,"NXP 74LVC245APW, TI SN74LVC245APW"
U8 ,1,AZ1117CH-3.3TRG1,stdpads:SOT-223,,Most 1117-type 3.3V regulator in SOT-223 package is acceptable.,C92102,"Diodes AZ1117CH-3.3TRG1, Diodes AZ1117EH-3.3TRG1"

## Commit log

2020-07-25 Create LICENSE
2020-07-25 Add GW4201D files
2020-08-02 Documentation update
2020-08-05 Fixed W9812/W9825 footprint
2020-09-11 Gitignore manual temp file
2020-09-11 Add pictures
2020-09-12 Update power consumption in manual
2020-09-18 Update GW4201DManual
2020-09-29 Switch to 7050 oscillator
2020-10-06 Fabbed 10/6/2020
2021-03-03 Fabbed
2021-04-29 Added 1.8V regulator
2021-04-29 Create folders for all board layouts
2021-04-29 Added source files
2021-04-29 Fix RAM4GS-ExtSPI.v
2021-04-29 Renamed AGM "in" signals
2021-04-29 Move stuff around
2021-05-01 finished MAX, LCMXO, iCE40?
2021-05-07 almost done
2021-05-22 more
2021-05-31 Generated gerbers and documenation PDFs
2021-05-31 Created BOMs
2021-06-01 Updated LCMXO2 board, fixed GND via
2021-06-01 Updated pos files
2021-06-01 Remove 3d models for DNP parts
2021-06-01 Rearrange pictures in documentaiton folder
2021-06-01 Add new renders
2021-06-01 Update FrontIsomTransparent
2021-06-01 BOM fixes
2021-06-01 Zip everything
2021-06-01 Remove stencil
2021-06-01 Add stencil zip files
2021-08-06 LED stuff
2021-08-16 MAX II and MAX V compiling?
2021-10-29 Fix LCMXO2 clock pin. Gerbers done.
2023-08-12 moved
2023-08-12 import
2023-08-13 so far so good
2023-08-13 With model detect
2023-08-13 Loads LED setting from UFM. On by defualt.
2023-08-13 Changed MAX detection scheme
2023-08-13 Led done?
2023-08-15 All compiling
2023-08-17 MachXO2 stuff
2023-08-17 Fixed wishbone bus
2023-08-20 MAX, MachXO, MachXO2 working
2023-08-20 Remove blobs
2023-08-20 Still good?
2023-09-29 Fixed failure to rewrite settings after UFM erase
2023-09-29 Gate LED with Ready signal
2023-11-03 2.1?
2023-11-07 Update Makefile
2023-11-07 LCMXO2: Add R12 and R13 to LCMXO2ZE BOM
2023-11-07 Fix LCMXO2ZE BOM filename
2023-11-11 Fixed LED and current-limiting resistor values in BOM
2024-01-07 SPI/LCMXO RC
2024-04-24 RC 2.2
2024-04-24 RC
    Remove MachXO crystal oscillator EN jumper under keepout area
    Remvoe DNP 3d models on MachXO2
2024-10-02 Add LCMXO2 internal oscillator firmware build
2025-02-23 RC D.2.3
